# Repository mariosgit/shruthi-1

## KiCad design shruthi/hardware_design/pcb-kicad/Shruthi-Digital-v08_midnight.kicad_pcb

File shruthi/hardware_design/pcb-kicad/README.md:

# How to convert a pcb

1. Start KICAD with no project opened
2. File / Import NOnKiCad.. / Eagle...
3. Select the board or schematics file you want to import.. (it will import both, no matter which you choose)
4. It will ask for a project dir, I would use ../pcb-kicad for all converted pcbs. If you choos existing proj dir, it will complain, ignore it say "no".
5. A Layer mapping dialog will open
   * Click the auto match button below
   * Now select "Milling" from the left list and double click "Edge.Cuts" under KiCAD Layers this will add this mapping to the list on the right.
   * Click OK
6. Save PCB and Schematic !
7. Try to F8 in the PCB, look if that removes things or not !?
8. Run a DRC check. Most of the "fails" are related to silkscreen, text, artwork and can be ignored, watch out for real problems on the copper layers.
9. Save again, Done.

# PS

If you convert all PCBs into one directory like I did, you need to **open the xy.pro file before** you can usefully edit the xy sch/brd.

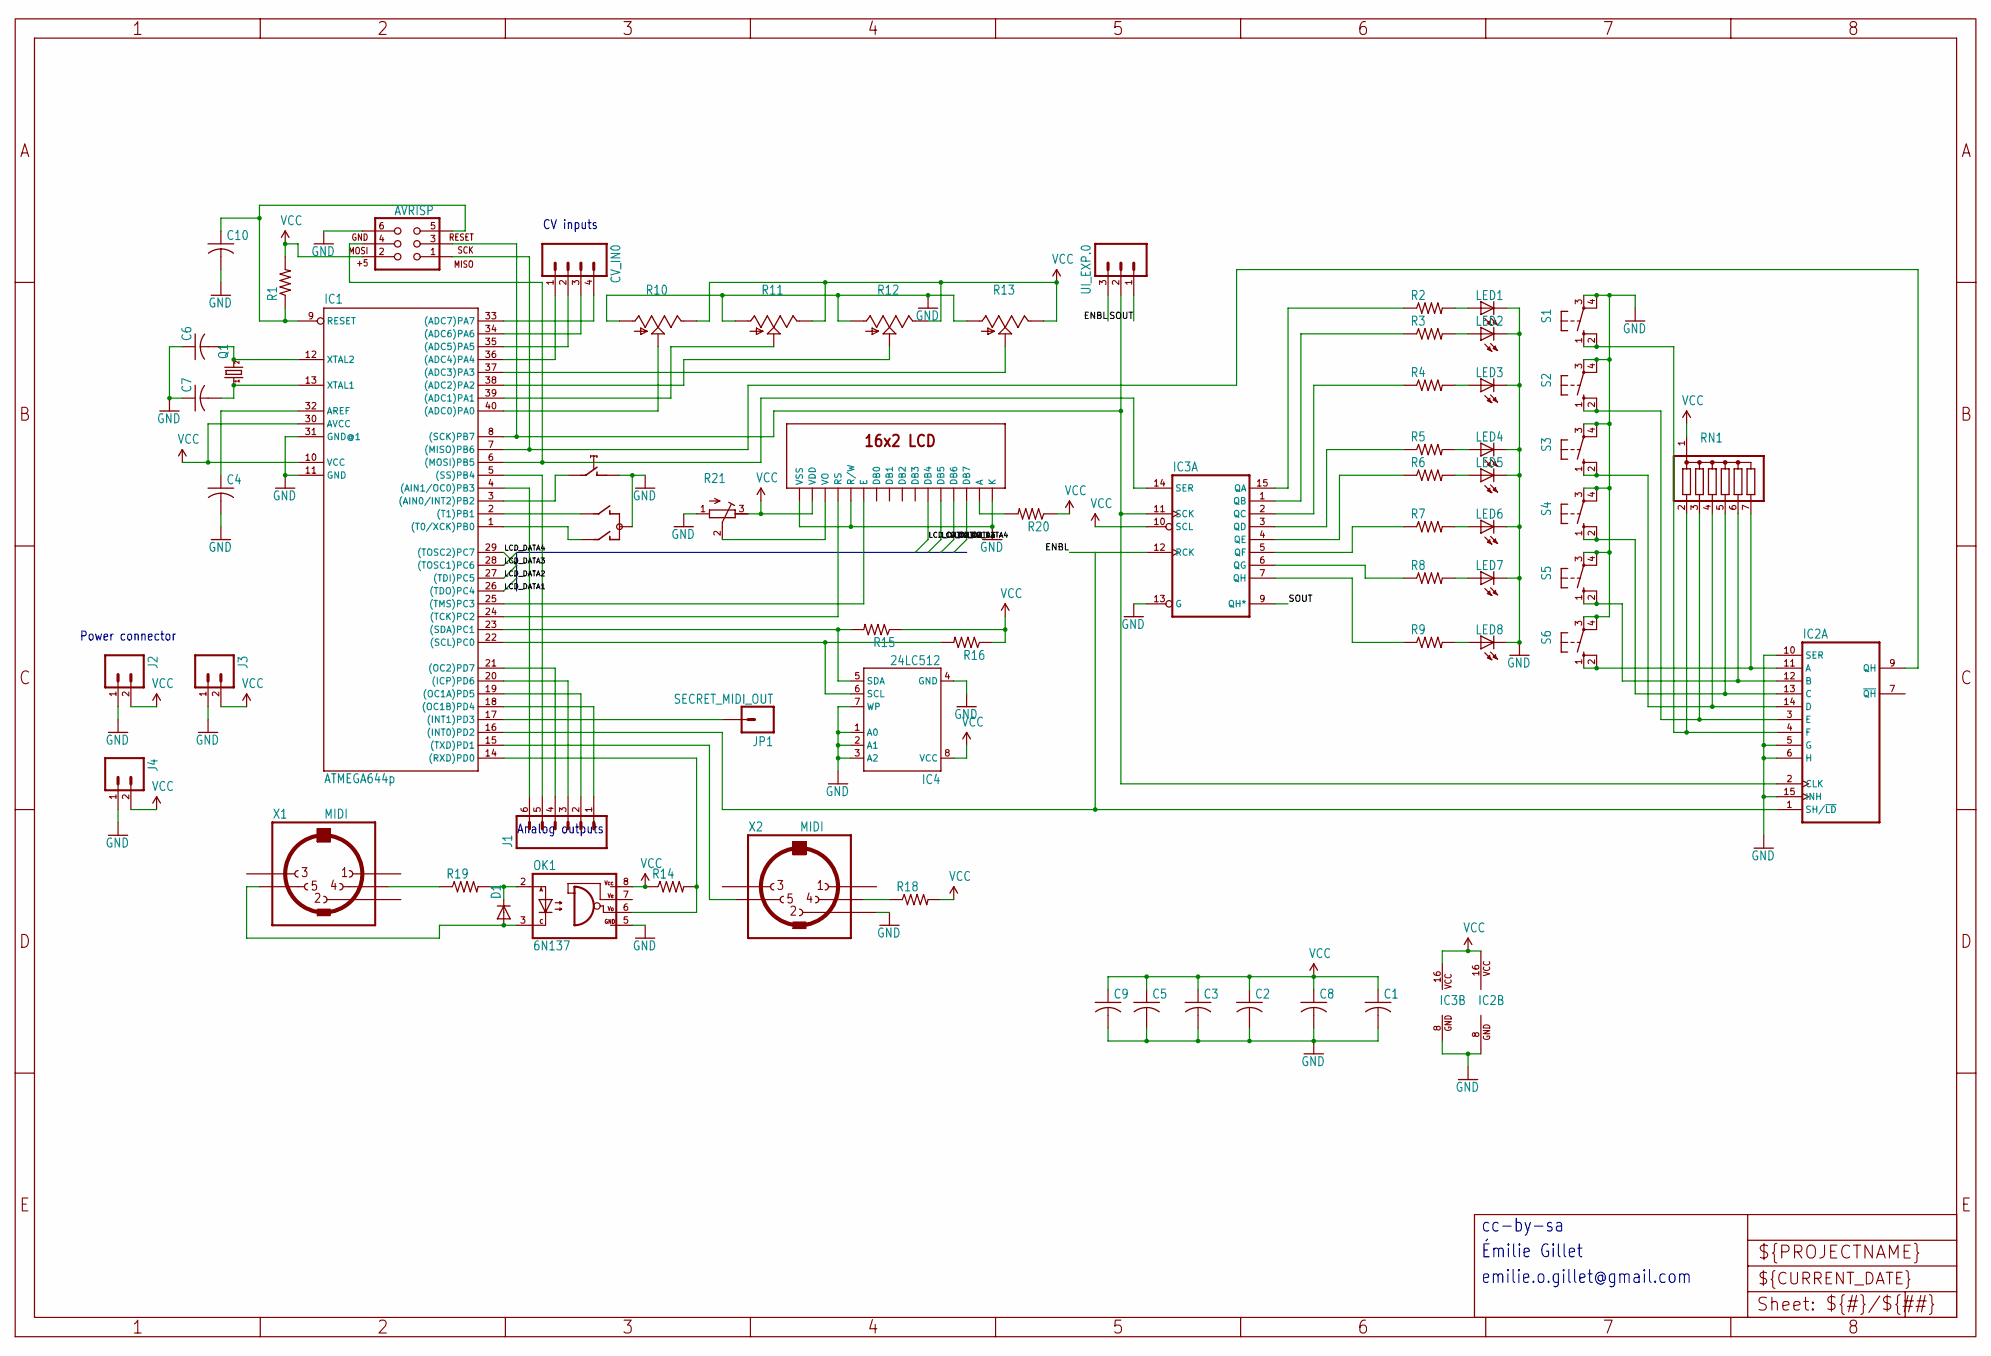
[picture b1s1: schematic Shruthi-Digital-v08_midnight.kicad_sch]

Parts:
C1, C2, C3, C4, C5, C6, C7, C8, C9, C10: C-US025-024X044; C025-024X044
CV_IN0: M04PTH; 1X04
D1: DIODE-D-5; D-5
IC1: ATMEGA644p; DIL40
IC2: 74165N; DIL16
IC3: 74595N; DIL16
IC4: 24LC512; DIL08
J1: M06SIP; 1X06
J2, J3, J4: M02PTH; 1X02
JP1: SECRET_MIDI_OUT; 1X01
LED1, LED2, LED3, LED4, LED5, LED6, LED7, LED8: LED3MM
OK1: 6N137; DIL08
Q1: CRYSTALHC49U-V; HC49U-V
R1, R2, R3, R4, R5, R6, R7, R8, R9, R14, R15, R16, R18, R19, R20: R-US_0204/7; 0204_7
R10, R11, R12, R13: POT_US; ALPS_POT_SFE
R21: R-TRIMM3296X; RTRIM3296X
RN1: G06R; SIL7
S1, S2, S3, S4, S5, S6: 40-XX; B3F-40XX
SW1: Encoder; ALPS_EC12E_SW
U1: AVRISP; 2X3
U$1: LCD-16X2
UI_EXP.0: M03PTH; 1X03
X1, X2: MIDI; MAB5SH

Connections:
/ENBL: IC1.16 ((INT0)PD2), IC2.1 (SH/~LD), IC3.12 (RCK), UI_EXP.0.3
/LCD_DATA1: IC1.26 ((TDO)PC4), U$1.11 (DB4)
/LCD_DATA2: IC1.27 ((TDI)PC5), U$1.12 (DB5)
/LCD_DATA3: IC1.28 ((TOSC1)PC6), U$1.13 (DB6)
/LCD_DATA4: IC1.29 ((TOSC2)PC7), U$1.14 (DB7)
/SOUT: IC3.9 (QH*), UI_EXP.0.1
GND: C1.2, C2.2, C3.2, C4.2, C5.2, C6.1, C7.1, C8.2, C9.2, C10.2, IC1.11 (GND), IC1.31 (GND@1), IC2.5 (G), IC2.6 (H), IC2.8 (GND), IC2.10 (SER), IC2.15 (INH), IC3.8 (GND), IC3.13 (G), IC4.1 (A0), IC4.2 (A1), IC4.3 (A2), IC4.4 (GND), IC4.7 (WP), J2.1, J3.1, J4.1, LED1.K (C), LED2.K (C), LED3.K (C), LED4.K (C), LED5.K (C), LED6.K (C), LED7.K (C), LED8.K (C), OK1.5 (GND), R10.P$3 (A), R11.P$3 (A), R12.P$3 (A), R13.P$3 (A), R21.1 (E), S1.3, S1.4 (P1), S2.3, S2.4 (P1), S3.3, S3.4 (P1), S4.3, S4.4 (P1), S5.3, S5.4 (P1), S6.3, S6.4 (P1), SW1.C, SW1.D (1), U1.6, U$1.1 (VSS), U$1.5 (R/W), U$1.16 (K), X2.2
unnamed: IC1.40 ((ADC0)PA0), R10.P$2 (S)
unnamed: IC1.39 ((ADC1)PA1), R11.P$2 (S)
unnamed: IC1.38 ((ADC2)PA2), R12.P$2 (S)
unnamed: IC1.37 ((ADC3)PA3), R13.P$2 (S)
unnamed: CV_IN0.1, IC1.36 ((ADC4)PA4)
unnamed: CV_IN0.2, IC1.35 ((ADC5)PA5)
unnamed: CV_IN0.3, IC1.34 ((ADC6)PA6)
unnamed: CV_IN0.4, IC1.33 ((ADC7)PA7)
unnamed: IC1.3 ((AIN0/INT2)PB2), SW1.E (2)
unnamed: IC1.4 ((AIN1/OC0)PB3), J1.6
unnamed: IC1.20 ((ICP)PD6), J1.3
unnamed: IC1.17 ((INT1)PD3), JP1.1
unnamed: IC1.7 ((MISO)PB6), IC2.9 (QH), U1.1
unnamed: IC1.6 ((MOSI)PB5), IC3.14 (SER), U1.4
unnamed: IC1.19 ((OC1A)PD5), J1.2
unnamed: IC1.18 ((OC1B)PD4), J1.1
unnamed: IC1.21 ((OC2)PD7), J1.4
unnamed: IC1.14 ((RXD)PD0), OK1.6 (VO), R14.2
unnamed: IC1.8 ((SCK)PB7), IC2.2 (CLK), IC3.11 (SCK), U1.3, UI_EXP.0.2
unnamed: IC1.22 ((SCL)PC0), IC4.6 (SCL), R16.2
unnamed: IC1.23 ((SDA)PC1), IC4.5 (SDA), R15.2
unnamed: IC1.5 ((SS)PB4), J1.5
unnamed: IC1.1 ((T0/XCK)PB0), SW1.A
unnamed: IC1.2 ((T1)PB1), SW1.B
unnamed: IC1.24 ((TCK)PC2), U$1.4 (RS)
unnamed: IC1.25 ((TMS)PC3), U$1.6 (E)
unnamed: IC1.15 ((TXD)PD1), X2.5
unnamed: C4.1, IC1.32 (AREF)
unnamed: C10.1, IC1.9 (RESET), R1.1, U1.5
unnamed: C7.2, IC1.13 (XTAL1), Q1.1
unnamed: C6.2, IC1.12 (XTAL2), Q1.2
unnamed: IC2.11 (A), RN1.7, S6.1 (S), S6.2 (S1)
unnamed: IC2.12 (B), RN1.6, S5.1 (S), S5.2 (S1)
unnamed: IC2.13 (C), RN1.5, S4.1 (S), S4.2 (S1)
unnamed: IC2.14 (D), RN1.4, S3.1 (S), S3.2 (S1)
unnamed: IC2.3 (E), RN1.3, S2.1 (S), S2.2 (S1)
unnamed: IC2.4 (F), RN1.2, S1.1 (S), S1.2 (S1)
unnamed: IC3.15 (QA), R2.1
unnamed: IC3.1 (QB), R3.1
unnamed: IC3.2 (QC), R4.1
unnamed: IC3.3 (QD), R5.1
unnamed: IC3.4 (QE), R6.1
unnamed: IC3.5 (QF), R7.1
unnamed: IC3.6 (QG), R8.1
unnamed: IC3.7 (QH), R9.1
unnamed: LED1.A, R2.2
unnamed: LED2.A, R3.2
unnamed: LED3.A, R4.2
unnamed: LED4.A, R5.2
unnamed: LED5.A, R6.2
unnamed: LED6.A, R7.2
unnamed: LED7.A, R8.2
unnamed: LED8.A, R9.2
unnamed: D1.C, OK1.2 (A), R19.2
unnamed: D1.A, OK1.3 (C), X1.5
unnamed: R18.1, X2.4
unnamed: R19.1, X1.4
unnamed: R21.2 (S), U$1.3 (VO)
unnamed: R20.2, U$1.15 (A)
VCC: C1.1, C2.1, C3.1, C5.1, C8.1, C9.1, IC1.10 (VCC), IC1.30 (AVCC), IC2.16 (VCC), IC3.10 (SCL), IC3.16 (VCC), IC4.8 (VCC), J2.2, J3.2, J4.2, OK1.8 (VCC), R1.2, R10.P$1 (E), R11.P$1 (E), R12.P$1 (E), R13.P$1 (E), R14.1, R15.1, R16.1, R18.2, R20.1, R21.3 (A), RN1.1, U1.2, U$1.2 (VDD)

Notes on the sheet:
Émilie Gillet
Power connector
cc-by-sa
emilie.o.gillet@gmail.com
Analog outputs
CV inputs

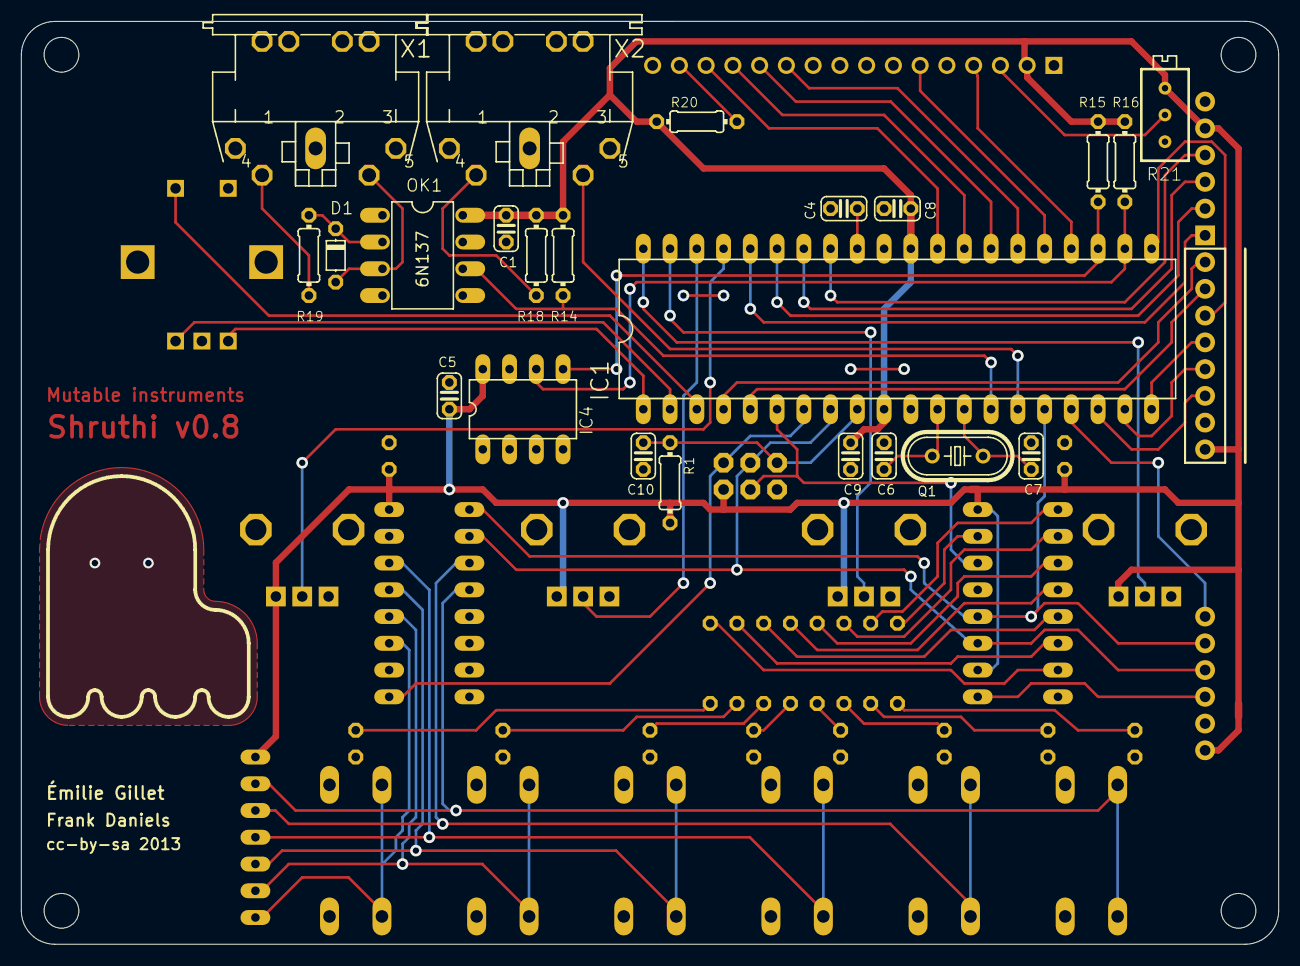
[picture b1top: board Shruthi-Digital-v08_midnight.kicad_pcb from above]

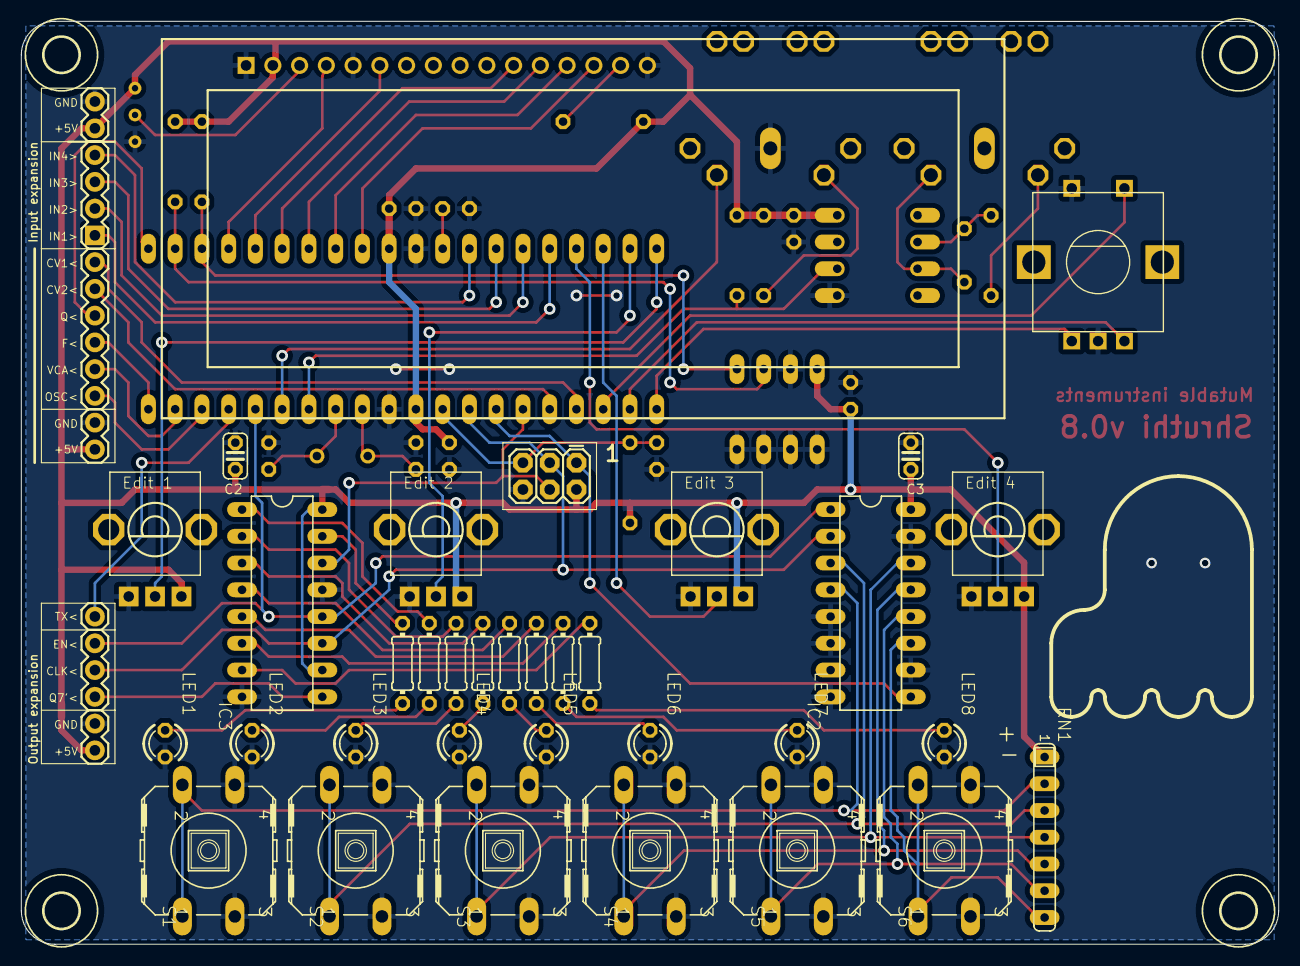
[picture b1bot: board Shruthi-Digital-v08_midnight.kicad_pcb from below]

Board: 2 copper layers, 119.4 x 87.6 mm, 68 parts (45 on the bottom side), 67 nets.

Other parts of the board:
U$2, U$3, U$4, U$5: 3,3

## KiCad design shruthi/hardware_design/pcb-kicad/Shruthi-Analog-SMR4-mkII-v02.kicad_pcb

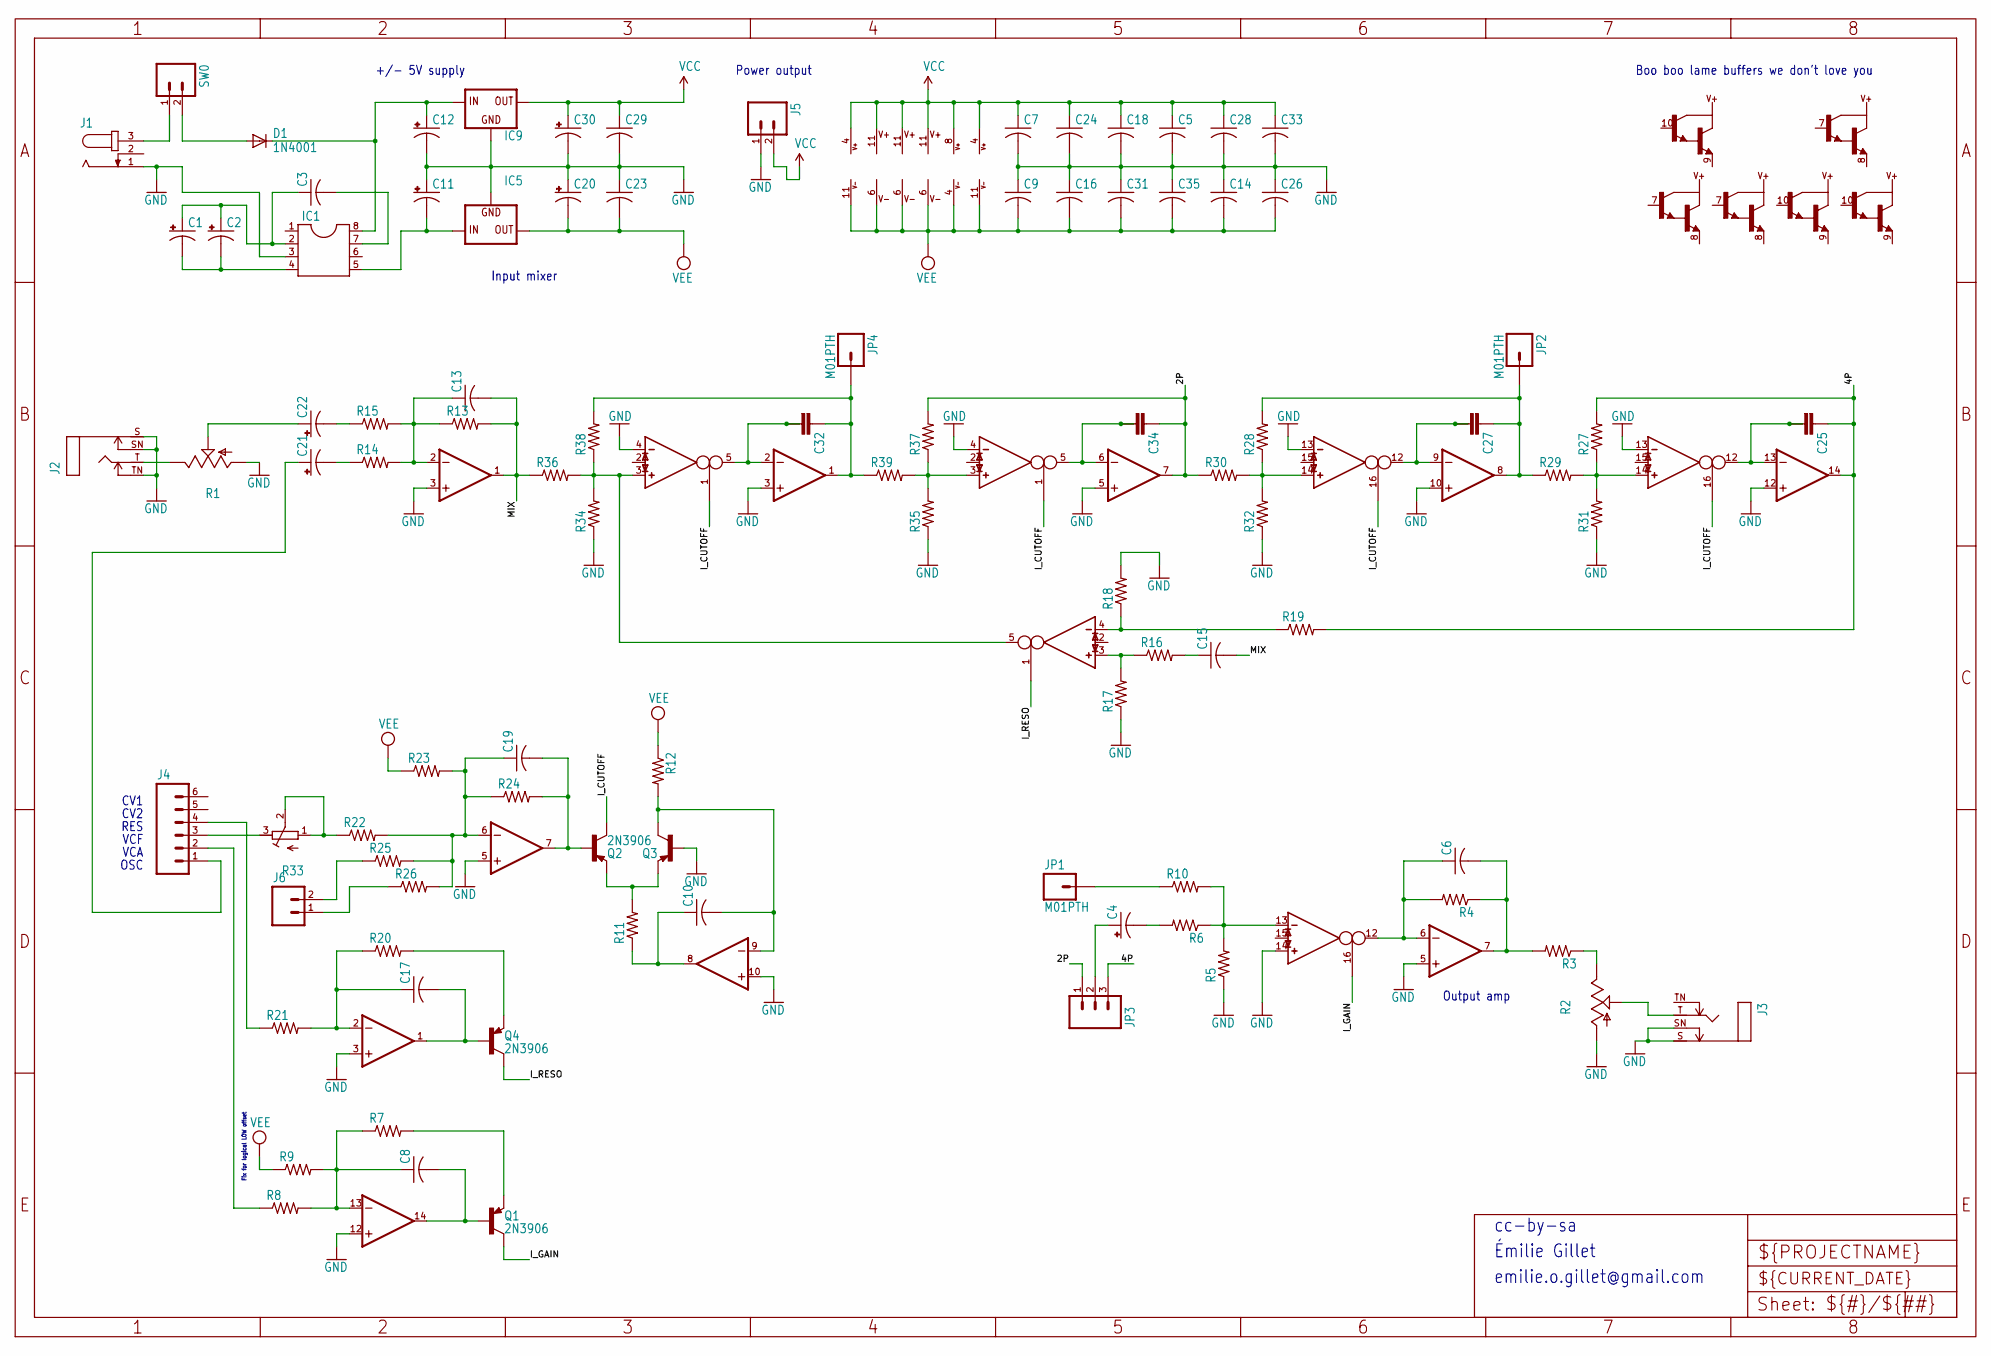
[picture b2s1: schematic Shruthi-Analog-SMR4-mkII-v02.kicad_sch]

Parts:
C1: CPOL-USE2.5-5; E2,5-5
C2, C4, C21, C22: CPOL-USE2.5-6; E2,5-6
C3, C5, C6, C7, C8, C9, C10, C13, C14, C15, C16, C17, C18, C19, C23, C24, C26, C28, C29, C31, C33, C35: C-US025-025X050; C025-025X050
C11, C12: CPOL-USE2.5-7; E2,5-7
C20, C30: CPOL-USE5-10.5; E5-10,5
C25, C27, C32, C34: C-2.5-5/2; C2.5_5-2
D1: 1N4001; DO41-10
IC1: DIL8; DIL08
IC2: TL072P; DIL08
IC3, IC6, IC8: LM13700N; DIL16
IC4, IC7: TL074P; DIL14
IC5: 79XXS
IC9: 78XXS
J1: JACK-PLUG2; SPC4078_BIG_HOLES
J2, J3: MONOSWS; NMJ4HC-S
J4: M06SIP; 1X06
J5, J6: M02PTH; 1X02
JP1, JP2, JP4: M01PTH; 1X01
JP3: M03PTH; 1X03
Q1, Q2, Q3, Q4: 2N3906; TO92-
R1, R2: POT_USCABLED; CABLE_POT_6MM
R3, R4, R5, R6, R7, R8, R9, R11, R12, R13, R14, R15, R16, R17, R18, R19, R20, R21, R22, R23, R24, R27, R28, R29, R30, R31, R32, R34, R35, R36, R37, R38, R39: R-US_0204/7; 0204_7
R10, R25, R26: R-US_0204/2V; 0204V
R33: R-TRIMM3296X; RTRIM3296X
SW0: M02PTH; 1X02

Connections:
/2P: C34.1, IC7.7 (OUT), JP3.1, R30.1, R37.2
/4P: C25.1, IC7.14 (OUT), JP3.3, R19.2, R27.2
/I_CUTOFF: IC6.1 (I_BIAS), IC6.16 (I_BIAS), IC8.1 (I_BIAS), IC8.16 (I_BIAS), Q2.1 (C)
/I_GAIN: IC3.16 (I_BIAS), Q1.1 (C)
/I_RESO: IC3.1 (I_BIAS), Q4.1 (C)
/MIX: C13.2, C15.2, IC2.1 (OUT), R13.2, R36.1
GND: C5.2, C7.2, C9.1, C11.+, C12.-, C14.1, C16.1, C18.2, C20.+, C23.1, C24.2, C26.1, C28.2, C29.2, C30.-, C31.1, C33.2, C35.1, IC1.3, IC2.3 (+IN), IC2.5 (+IN), IC3.14 (IN_P), IC4.3 (+IN), IC4.5 (+IN), IC4.10 (+IN), IC4.12 (+IN), IC5.GND, IC6.4 (IN_N), IC6.13 (IN_N), IC7.3 (+IN), IC7.5 (+IN), IC7.10 (+IN), IC7.12 (+IN), IC8.4 (IN_N), IC8.13 (IN_N), IC9.GND, J1.1, J2.S, J2.SN, J2.TN, J3.S, J3.SN, J5.1, Q3.2 (B), R1.A, R2.A, R5.1, R17.1, R18.2, R31.1, R32.1, R34.1, R35.1
unnamed: C1.+, C2.+, C3.1, IC1.2
unnamed: C1.-, C2.-, IC1.4
unnamed: C3.2, IC1.7
unnamed: C4.+, JP3.2
unnamed: C4.-, R6.2
unnamed: C11.-, IC1.5, IC5.IN
unnamed: C12.+, D1.C, IC1.8, IC9.IN
unnamed: C15.1, R16.2
unnamed: C21.+, J4.1
unnamed: C21.-, R14.1
unnamed: C22.+, R1.S
unnamed: C22.-, R15.1
unnamed: D1.A, SW0.2
unnamed: C13.1, IC2.2 (-IN), R13.1, R14.2, R15.2
unnamed: C6.1, IC2.6 (-IN), IC3.12 (OUT), R4.2
unnamed: C6.2, IC2.7 (OUT), R3.2, R4.1
unnamed: IC3.4 (IN_N), R18.1, R19.1
unnamed: IC3.3 (IN_P), R16.1, R17.2
unnamed: IC3.5 (OUT), IC6.3 (IN_P), R34.2, R36.2, R38.1
unnamed: IC3.13 (IN_N), R5.2, R6.1, R10.2
unnamed: C17.1, IC4.2 (-IN), R20.1, R21.2
unnamed: C17.2, IC4.1 (OUT), Q4.2 (B)
unnamed: C19.1, IC4.6 (-IN), R22.2, R23.2, R24.1, R25.2, R26.2
unnamed: C19.2, IC4.7 (OUT), Q2.2 (B), R24.2
unnamed: C10.2, IC4.9 (-IN), Q3.1 (C), R12.2
unnamed: C10.1, IC4.8 (OUT), R11.1
unnamed: C8.1, IC4.13 (-IN), R7.1, R8.2, R9.2
unnamed: C8.2, IC4.14 (OUT), Q1.2 (B)
unnamed: C32.2, C32.3, IC6.5 (OUT), IC7.2 (-IN)
unnamed: IC6.14 (IN_P), R27.1, R29.2, R31.2
unnamed: C25.2, C25.3, IC6.12 (OUT), IC7.13 (-IN)
unnamed: C32.1, IC7.1 (OUT), JP4.1, R38.2, R39.1
unnamed: C34.2, C34.3, IC7.6 (-IN), IC8.5 (OUT)
unnamed: C27.2, C27.3, IC7.9 (-IN), IC8.12 (OUT)
unnamed: C27.1, IC7.8 (OUT), JP2.1, R28.2, R29.1
unnamed: IC8.3 (IN_P), R35.2, R37.1, R39.2
unnamed: IC8.14 (IN_P), R28.1, R30.2, R32.2
unnamed: J1.3, SW0.1
unnamed: J2.T, R1.E
unnamed: J3.T, R2.S
unnamed: J4.2, R8.1
unnamed: J4.4, R21.1
unnamed: J6.1, R26.1
unnamed: J6.2, R25.1
unnamed: JP1.1, R10.1
unnamed: Q1.3 (E), R7.2
unnamed: Q2.3 (E), Q3.3 (E), R11.2
unnamed: Q4.3 (E), R20.2
unnamed: R2.E, R3.1
unnamed: J4.3, R33.3 (A)
unnamed: R22.1, R33.1 (E), R33.2 (S)
VCC: C5.1, C7.1, C18.1, C24.1, C28.1, C29.1, C30.+, C33.1, IC2.8 (V+), IC3.11 (V+), IC4.4 (V+), IC6.11 (V+), IC7.4 (V+), IC8.11 (V+), IC9.OUT, J5.2
VEE: C9.2, C14.2, C16.2, C20.-, C23.2, C26.2, C31.2, C35.2, IC2.4 (V-), IC3.6 (V-), IC4.11 (V-), IC5.OUT, IC6.6 (V-), IC7.11 (V-), IC8.6 (V-), R9.1, R12.1, R23.1

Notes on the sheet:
cc-by-sa
Boo boo lame buffers we don't love you
emilie.o.gillet@gmail.com
Input mixer
VCF
Fix for logical LOW offset
CV2
OSC
RES
Power output
Émilie Gillet
VCA
+/- 5V supply
CV1
Output amp

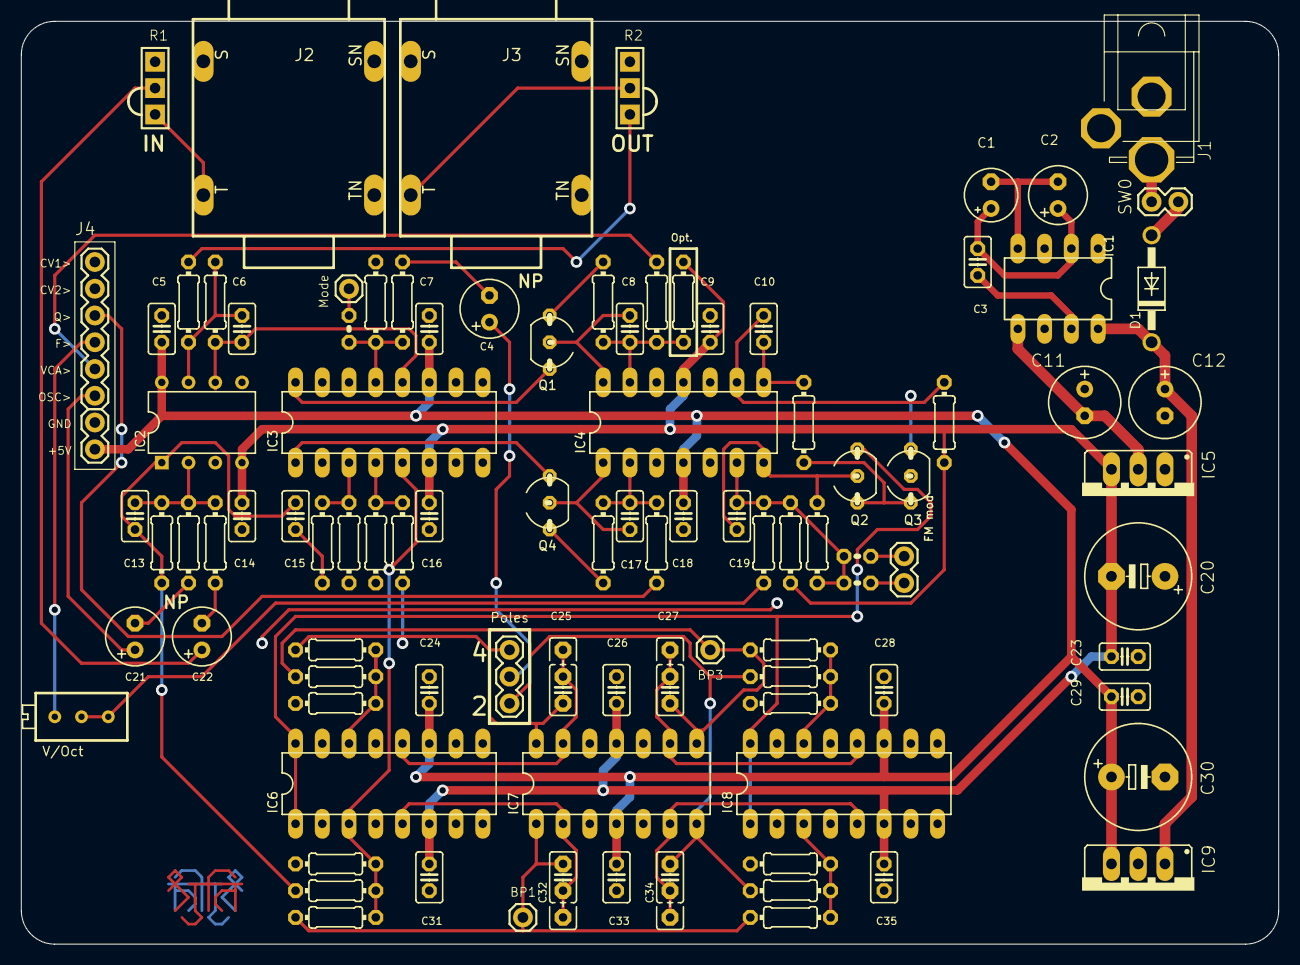
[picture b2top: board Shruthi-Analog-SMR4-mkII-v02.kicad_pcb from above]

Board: 2 copper layers, 119.4 x 87.6 mm, 99 parts (0 on the bottom side), 60 nets.

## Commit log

2024-07-02 saved as eagle 9.x (xml), KiCADable.
2024-07-02 Added 2 kicad conversions

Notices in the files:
shruthi/hardware_design/pcb-kicad/Shruthi-Digital-v08_midnight.kicad_pcb:
cc-by-sa 2013
